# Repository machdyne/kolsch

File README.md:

# Kölsch Computer

Kölsch is an FPGA computer based on the GateMate A1.

This repo contains schematics, PCB layouts, pinouts, a 3D-printable case, example gateware and documentation.

Find more information on the [Kölsch product page](https://machdyne.com/product/kolsch-computer/).

## Programming Kölsch 

Kölsch can be programmed over USB-C or by copying gateware to a MicroSD card. The FPGA is configured by the onboard RP2040, which can load the configuration from onboard flash, a FAT-formatted MicroSD card or over the USB-JTAG bridge.

### JTAG

Program the FPGA configuration SRAM:

```
openFPGALoader -c dirtyJtag image.bit
```

## Examples

In order to build the examples, first edit rtl/config.mk and set the paths to the location of your toolchain. You can download the toolchain from [Cologne Chip](https://colognechip.com).

You can build each example with:

```
$ make && make impl
```

### 3.5mm TRRS Audio Jack

| Pin | Signal |
| --- | ------ |
| T | Left Audio |
| R1 | Right Audio |
| R2 | Composite Video |
| S | GND |

## Resources

 * [fpga-dac audio player](https://github.com/machdyne/fpga-dac)

## Board Revisions

| Revision | Notes |
| -------- | ----- |
| V2 | Initial production version |

## Funding

This project was partially funded through the NGI0 Entrust Fund, a fund established by NLnet with financial support from the European Commission's Next Generation Internet programme.

## License

This project is released under the [CERN-OHL-P](LICENSE.txt) license.

Note: You can use these designs for commercial purposes but we ask that instead of producing exact clones, that you either replace our trademarks and logos with your own or add your own next to ours.

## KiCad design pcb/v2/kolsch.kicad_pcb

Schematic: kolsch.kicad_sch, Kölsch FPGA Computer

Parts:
C1, C2, C3, C12, C16, C18, C19, C27, C28, C38, C39, C48, C49, C69, C70: 2.2uF; C_0603_1608Metric
C4, C5, C6, C21, C22, C29, C30, C41, C42, C50, C51, C75, C76: 470nF; C_0603_1608Metric
C7: 220nF; C_0402_1005Metric
C8, C9, C10, C11, C15, C17, C23, C24, C31, C32, C33, C34, C35, C43, C44, C45, C46, C47, C52, C53, C55, C56, C78, C79, C80, C81, C103, C104, C105, C106, C107: 100nF; C_0402_1005Metric
C13, C14, C25, C26: 10nF; C_0402_1005Metric
C20, C36, C37, C58, C59, C61, C62, C64, C65, C66, C67, C68, C71, C74, C77, C82, C84, C86, C87: 100nF; C_0603_1608Metric
C40, C72, C73, C97, C98, C101: 10uF; C_0603_1608Metric
C54, C57: 15pF; C_0603_1608Metric
C60, C63, C83, C85, C88: 1uF; C_0603_1608Metric
C89, C90, C91: 4.7uF; C_0603_1608Metric
C92: 10uF; R_0603_1608Metric
C93: 100nF; R_0603_1608Metric
C94, C95, C96: 10pF; C_0603_1608Metric
C99, C100, C102: 22uF; C_0603_1608Metric
C109, C110: 10uF; C_0402_1005Metric
D1: LED; LED_1206_3216Metric
FB3, FB4, FB5: Ferrite_Bead; R_0603_1608Metric
H1, H2, H3, H4: MountingHole_Pad; MountingHole_3.2mm_M3_Pad
J1: TYPE-C-31-M-12-FIXED; USB_C_Receptacle_HRO_TYPE-C-31-M-12-BIG-PADS-PASTE; PARTREV A
J2: USB_A_Stacked; USB_A_Wuerth_61400826021_Horizontal_Stacked
J3: AudioJack4; Jack_3.5mm_PJ320D_Horizontal
J4: MICROSD; SDCARD
L1, L2, L3: 2.2uH; L_Taiyo-Yuden_MD-4040
PMOD1: PMOD-Device-x2-Type-1A-GPIO; PMOD_2x06_HOST
R1, R3, R4, R5, R8: 4K7; R_0603_1608Metric
R2, R10: 5K1; R_0603_1608Metric
R6, R7: 27R; R_0603_1608Metric
R9, R17, R18, R26, R27, R28, R29, R40, R41: 0R; LD-NETTIE-0603
R11, R12, R20, R21: 15K; R_0402_1005Metric
R13, R14, R15, R16: 22R; R_0402_1005Metric
R19, R58, R65: 200K; R_0603_1608Metric
R30, R35, R38, R45, R49, R53: 1K; R_0603_1608Metric
R31, R32, R63, R64: 100R; R_0603_1608Metric
R33, R42, R43, R47, R51: 270R; R_0603_1608Metric
R34, R44, R48, R52: 536R; R_0603_1608Metric
R36: 2K; R_0603_1608Metric
R37: 10K; R_0603_1608Metric
R39: 33R; R_0603_1608Metric
R46, R50, R54: 2K2; R_0603_1608Metric
R55, R56, R57: 68R; R_0603_1608Metric
R59, R60, R61, R62: 20K; R_0603_1608Metric
R66: 44K2; R_0603_1608Metric
R67: 150K; R_0603_1608Metric
R68: 47K; R_0603_1608Metric
R69: 100K; R_0603_1608Metric
R70: 120K; R_0603_1608Metric
R73: 22R; R_0603_1608Metric
SW1: BOOT; Button_2P_3x4mm
TP1: TP_PWR1V8; TestPoint_THTPad_D1.0mm_Drill0.5mm
TP2: TP_PWR3V3; TestPoint_THTPad_D1.0mm_Drill0.5mm
TP3: TP_PWR2V5; TestPoint_THTPad_D1.0mm_Drill0.5mm
TP4: TP_PWR1V1; TestPoint_THTPad_D1.0mm_Drill0.5mm
U1: CCGM1A1; BGA-324_15.0x15.0mm_Layout18x18_P0.8mm_Ball0.5mm_Pad0.4mm_N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
U2: W989D6DBGX6; W989D6DB; PARTREV A05
U3, U8: LSF0108PWR; TSSOP-20_4.4x6.5mm_P0.65mm
U4: RP2040; RP2040-QFN-56-OFFICIAL; PARTREV 1.6.1
U5: AT25FF321A-SSHN-B; SOIC-8_3.9x4.9mm_P1.27mm
U6: 48MHz; OSC_KC2016Z13.5600C1KX00
U7: NCP164ASN180T1G; SOT-23-5
U9, U10, U11: TLV62569DDC; SOT-23-6
VGA1: DB15_Female_MountingHoles; DSUB-15-HD_Female_Horizontal_P2.29x1.98mm_EdgePinOffset3.03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
Y1: ECS-80-12-33-JGN-TR-12MHZ; XTAL_ECS-240-8-33-AGN-TR

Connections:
/AUDIO_L: R31.1, U1.A9 (IO_NB_B0)
/AUDIO_LC: C72.1, J3.T
/AUDIO_R: R32.1, U1.B9 (IO_NB_A0)
/AUDIO_RC: C73.1, J3.R1
/BOOT: R38.1, SW1.1
/CDONE: U1.V3 (IO_WA_B2/CFG_DONE), U4.27 (GPIO16)
/CFAILED: R1.2, U1.V2 (IO_WA_A2/~CFG_FAILED), U4.28 (GPIO17)
/CFG_MD2: U1.U4 (CFG_MD2/IO_WA_A1), U4.18 (GPIO15)
/CFG_MD3: U1.V4 (CFG_MD3/IO_WA_B1), U4.17 (GPIO14)
/CLK48: U1.N14 (CLK0/IO_SB_A8), U6.3 (CLK)
/CRESET: U1.T15 (~RESET), U4.11 (GPIO8)
/CSD_MISO: U1.E2 (IO_WC_B3), U3.6 (A4), U4.6 (GPIO4)
/CSD_MOSI: U1.E1 (IO_WC_A3), U3.5 (A3), U4.9 (GPIO7)
/CSD_SCK: U1.E3 (IO_WC_A4), U3.4 (A2), U4.8 (GPIO6)
/CSD_SS: U1.D2 (IO_WC_B5), U3.3 (A1), U4.7 (GPIO5)
/CUSB1_DN: U1.H2 (IO_WB_B7), U3.10 (A8), U4.13 (GPIO10)
/CUSB1_DP: U1.H1 (IO_WB_A7), U3.9 (A7), U4.14 (GPIO11)
/CUSB2_DN: U1.K2 (IO_WB_B5), U3.8 (A6), U4.15 (GPIO12)
/CUSB2_DP: U1.K1 (IO_WB_A5), U3.7 (A5), U4.16 (GPIO13)
/DRAM_A0: U1.K18 (IO_EA_A2), U2.H7 (A0)
/DRAM_A1: U1.P18 (IO_SB_B2), U2.H8 (A1)
/DRAM_A2: U1.N15 (IO_SB_B8), U2.J8 (A2)
/DRAM_A3: U1.K17 (IO_EA_B2), U2.J7 (A3)
/DRAM_A4: U1.M14 (IO_EA_B0), U2.J3 (A4)
/DRAM_A5: U1.M15 (IO_EA_A0), U2.J2 (A5)
/DRAM_A6: U1.P15 (IO_SB_B6), U2.H3 (A6)
/DRAM_A7: U1.M17 (IO_SB_A3), U2.H2 (A7)
/DRAM_A8: U1.L16 (IO_EA_A1), U2.H1 (A8)
/DRAM_A9: U1.U18 (IO_SB_B0), U2.G3 (A9)
/DRAM_A10: U1.P17 (IO_SB_A2), U2.H9 (A10)
/DRAM_A11: U1.U17 (IO_SB_A0), U2.G2 (A11)
/DRAM_A12: U1.L15 (IO_EA_B1), U2.G1 (A12)
/DRAM_BS0: U1.J17 (IO_EA_B4), U2.G7 (BA0)
/DRAM_BS1: U1.R18 (IO_SB_B1), U2.G8 (BA1)
/DRAM_CAS: U1.M18 (IO_SB_B3), U2.F7 (~CAS)
/DRAM_CKE: U1.R10 (IO_SA_A7), U2.F3 (CKE)
/DRAM_CLK: U1.R9 (IO_SA_A6), U2.F2 (CLK)
/DRAM_CS: U1.R17 (IO_SB_A1), U2.G9 (~CS)
/DRAM_DQ0: U1.V8 (IO_SA_B5), U2.A8 (DQ0)
/DRAM_DQ1: U1.T8 (IO_SA_B4), U2.B9 (DQ1)
/DRAM_DQ2: U1.U8 (IO_SA_A5), U2.B8 (DQ2)
/DRAM_DQ3: U1.P13 (IO_SB_B7), U2.C9 (DQ3)
/DRAM_DQ4: U1.T10 (IO_SA_B7), U2.C8 (DQ4)
/DRAM_DQ5: U1.P14 (CLK2/IO_SB_A6), U2.D9 (DQ5)
/DRAM_DQ6: U1.T9 (IO_SA_B6), U2.D8 (DQ6)
/DRAM_DQ7: U1.V10 (IO_SA_B8), U2.E9 (DQ7)
/DRAM_DQ8: U1.R7 (IO_SA_A2), U2.E1 (DQ8)
/DRAM_DQ9: U1.R8 (IO_SA_A4), U2.D2 (DQ9)
/DRAM_DQ10: U1.T7 (IO_SA_B2), U2.D1 (DQ10)
/DRAM_DQ11: U1.V5 (IO_SA_B0), U2.C2 (DQ11)
/DRAM_DQ12: U1.U5 (IO_SA_A0), U2.C1 (DQ12)
/DRAM_DQ13: U1.V7 (IO_SA_B3), U2.B2 (DQ13)
/DRAM_DQ14: U1.T6 (IO_SA_B1), U2.B1 (DQ14)
/DRAM_DQ15: U1.U7 (IO_SA_A3), U2.A2 (DQ15)
/DRAM_LDQM: U1.U10 (IO_SA_A8), U2.E8 (LDQM)
/DRAM_RAS: U1.R14 (IO_SB_B5), U2.F8 (~RAS)
/DRAM_UDQM: U1.R6 (IO_SA_A1), U2.F1 (UDQM)
/DRAM_WE: U1.R13 (CLK3/IO_SB_A5), U2.F9 (~WE)
/JTAG_TCK: R3.2, U1.R3 (JTAG_TCK/IO_WA_A5), U4.29 (GPIO18)
/JTAG_TDI: R5.2, U1.T2 (JTAG_TDI/IO_WA_A4), U4.31 (GPIO20)
/JTAG_TDO: R8.2, U1.U2 (JTAG_TDO/IO_WA_B3), U4.32 (GPIO21)
/JTAG_TMS: R4.2, U1.T3 (JTAG_TMS/IO_WA_B4), U4.30 (GPIO19)
/LED: R42.1, U1.A12 (IO_NB_B4)
/PMOD_A1: U1.D17 (IO_EB_B2), U8.3 (A1)
/PMOD_A1C: PMOD1.1 (IOA0), U8.18 (B1)
/PMOD_A2: U1.D18 (IO_EB_A2), U8.4 (A2)
/PMOD_A2C: PMOD1.2 (IOA1), U8.17 (B2)
/PMOD_A3: U1.E15 (IO_EB_B3), U8.5 (A3)
/PMOD_A3C: PMOD1.3 (IOA2), U8.16 (B3)
/PMOD_A4: U1.E16 (IO_EB_A3), U8.6 (A4)
/PMOD_A4C: PMOD1.4 (IOA3), U8.15 (B4)
/PMOD_A7: U1.F18 (IO_EB_A0), U8.7 (A5)
/PMOD_A7C: PMOD1.7 (IOB0), U8.14 (B5)
/PMOD_A8: U1.F17 (IO_EB_B0), U8.8 (A6)
/PMOD_A8C: PMOD1.8 (IOB1), U8.13 (B6)
/PMOD_A9: U1.F16 (IO_EB_A1), U8.9 (A7)
/PMOD_A9C: PMOD1.9 (IOB2), U8.12 (B7)
/PMOD_A10: U1.F15 (IO_EB_B1), U8.10 (A8)
/PMOD_A10C: PMOD1.10 (IOB3), U8.11 (B8)
/PWR1V0: C58.1, C61.1, C63.1, U4.23 (DVDD), U4.45 (VREG_VOUT), U4.50 (DVDD)
/PWR1V1: C1.2, C2.2, C4.2, C5.2, C9.2, C10.2, C13.2, C14.2, C18.2, C19.2, C20.2, C21.2, C22.2, C23.2, C24.2, C25.2, C26.2, C96.1, C99.1, C100.1, L3.2, R69.1, R73.2, TP4.1, U1.F9 (VDD), U1.G6 (VDD), U1.G8 (VDD), U1.G10 (VDD), U1.G12 (VDD), U1.H7 (VDD), U1.H9 (VDD), U1.H11 (VDD), U1.H13 (VDD), U1.J6 (VDD), U1.J8 (VDD), U1.J10 (VDD), U1.J12 (VDD), U1.K7 (VDD), U1.K9 (VDD), U1.K11 (VDD), U1.K13 (VDD), U1.L6 (VDD), U1.L8 (VDD), U1.L10 (VDD), U1.L12 (VDD), U1.M7 (VDD), U1.M9 (VDD), U1.M11 (VDD), U1.M13 (VDD), U1.N6 (VDD), U1.N8 (VDD), U1.N10 (VDD)
/PWR1V8: C84.1, C88.1, C103.2, C104.2, C105.2, C106.2, C107.2, C109.2, C110.2, R27.2, R28.2, R29.2, TP1.1, U2.A7 (VDDQ), U2.A9 (VDD), U2.B3 (VDDQ), U2.C7 (VDDQ), U2.D3 (VDDQ), U2.E7 (VDD), U2.J9 (VDD), U6.1 (INH), U6.4 (VCC), U7.5 (OUT)
/PWR2V5: C8.2, C16.2, C37.1, C60.1, C62.1, C64.1, C65.1, C68.1, C71.1, C74.1, C77.1, C82.1, C83.1, C87.1, C95.1, C98.1, L2.2, R1.1, R4.1, R5.1, R8.1, R9.2, R17.2, R18.2, R26.2, R40.2, R41.2, R67.1, TP3.1, U1.T14 (VDD_CLK), U3.2 (VREF_A), U4.1 (IOVDD), U4.10 (IOVDD), U4.22 (IOVDD), U4.26 (RUN), U4.33 (IOVDD), U4.42 (IOVDD), U4.43 (ADC_AVDD), U4.44 (VREG_VIN), U4.49 (IOVDD), U5.8 (VCC), U8.2 (VREF_A)
/PWR3V3: C59.1, C85.1, C92.1, C93.1, C94.1, C97.1, C101.1, J4.4 (VDD), L1.2, PMOD1.6 (VCC), PMOD1.12 (VCC), R19.1, R37.1, R58.1, R59.1, R60.1, R61.1, R62.1, R65.1, TP2.1, U4.48 (USB_VDD), U7.1 (IN), U7.3 (EN)
/PWR5V0: C89.1, C90.1, C91.1, FB3.1, FB4.1, FB5.1, U9.1 (EN), U9.4 (VIN), U10.1 (EN), U10.4 (VIN), U11.1 (EN), U11.4 (VIN)
/RP_QSPI_IO0: U4.53 (QSPI_SD0), U5.5 (DI(IO0))
/RP_QSPI_IO1: U4.55 (QSPI_SD1), U5.2 (DO(IO1))
/RP_QSPI_IO2: U4.54 (QSPI_SD2), U5.3 (IO2)
/RP_QSPI_IO3: U4.51 (QSPI_SD3), U5.7 (IO3)
/RP_QSPI_SCK: U4.52 (QSPI_SCLK), U5.6 (CLK)
/RP_QSPI_SS: R37.2, R38.2, U4.56 (QSPI_CSN), U5.1 (~CS)
/RSPI_MISO: U1.P1 (IO_WA_A7/SPI_D1), U4.40 (GPIO28/ADC2)
/RSPI_MOSI: U1.P2 (IO_WA_B7/SPI_D0), U4.39 (GPIO27/ADC1)
/RSPI_SCK: U1.N4 (IO_WA_B8/SPI_CLK), U4.38 (GPIO26/ADC0)
/RSPI_SS: U1.N3 (IO_WA_A8/~SPI_CS), U4.41 (GPIO29/ADC3)
/RUART_RX: U1.F3 (IO_WC_A2), U4.37 (GPIO25)
/RUART_TX: U1.G1 (IO_WC_A0), U4.36 (GPIO24)
/SD_MISO: J4.7 (DAT0), R62.2, U3.15 (B4)
/SD_MOSI: J4.3 (CMD), R60.2, U3.16 (B3)
/SD_SCK: J4.5 (CLK), R61.2, U3.17 (B2)
/SD_SS: J4.2 (DAT3/CD), R59.2, U3.18 (B1)
/SWCLK: U4.24 (SWCLK)
/SWD: U4.25 (SWD)
/USB1_CONN_DN: J2.2 (D1-), R14.1, R21.1
/USB1_CONN_DP: J2.3 (D1+), R13.1, R20.1
/USB1_DN: R14.2, U3.11 (B8)
/USB1_DP: R13.2, U3.12 (B7)
/USB2_CONN_DN: J2.6 (D2-), R12.1, R16.1
/USB2_CONN_DP: J2.7 (D2+), R11.1, R15.1
/USB2_DN: R16.2, U3.13 (B6)
/USB2_DP: R15.2, U3.14 (B5)
/USB_CONN_DN: J1.A7 (DN1), J1.B7 (DN2), R6.1
/USB_CONN_DP: J1.A6 (DP1), J1.B6 (DP2), R7.1
/USB_DN: R6.2, U4.46 (USB_DM)
/USB_DP: R7.2, U4.47 (USB_DP)
/VBUSC: FB3.2, FB4.2, J1.A4 (VBUS), J1.A9 (VBUS), J1.B4 (VBUS), J1.B9 (VBUS)
/VDD_EA: C39.2, C42.2, C44.2, C46.2, R27.1, U1.G14 (VDD_EA), U1.H17 (VDD_EA), U1.J14 (VDD_EA), U1.L14 (VDD_EA), U1.L17 (VDD_EA)
/VDD_EB: C38.2, C41.2, C43.2, C45.2, C47.2, R26.1, U1.A16 (VDD_EB), U1.B18 (VDD_EB), U1.E14 (VDD_EB), U1.E17 (VDD_EB), U1.F13 (VDD_EB)
/VDD_NA: C27.2, C29.2, C31.2, C33.2, C35.2, R17.1, U1.A5 (VDD_NA), U1.B7 (VDD_NA), U1.E6 (VDD_NA), U1.E8 (VDD_NA), U1.F7 (VDD_NA)
/VDD_NB: C28.2, C30.2, C32.2, C34.2, R18.1, U1.B10 (VDD_NB), U1.B13 (VDD_NB), U1.E10 (VDD_NB), U1.E12 (VDD_NB), U1.F11 (VDD_NB)
/VDD_PLL: C7.2, C12.2, C102.2, R73.1, U1.P16 (VDD_PLL)
/VDD_SA: C49.2, C51.2, C53.2, C56.2, R29.1, U1.P6 (VDD_SA), U1.P8 (VDD_SA), U1.P10 (VDD_SA), U1.U6 (VDD_SA), U1.U9 (VDD_SA)
/VDD_SB: C48.2, C50.2, C52.2, C55.2, R28.1, U1.N11 (VDD_SB), U1.N13 (VDD_SB), U1.N18 (VDD_SB), U1.R15 (VDD_SB), U1.T18 (VDD_SB)
/VDD_WA: C3.2, C6.2, C11.2, C15.2, C17.2, R9.1, U1.N5 (VDD_WA), U1.P3 (VDD_WA), U1.P5 (VDD_WA), U1.T1 (VDD_WA), U1.U3 (VDD_WA)
/VDD_WB: C70.2, C76.2, C79.2, C81.2, R41.1, U1.H5 (VDD_WB), U1.J2 (VDD_WB), U1.K5 (VDD_WB), U1.M2 (VDD_WB), U1.M5 (VDD_WB)
/VDD_WC: C69.2, C75.2, C78.2, C80.2, R40.1, U1.A2 (VDD_WC), U1.C2 (VDD_WC), U1.D5 (VDD_WC), U1.F2 (VDD_WC), U1.F5 (VDD_WC)
/VGA_B0: R51.2, U1.C9 (IO_NA_A8)
/VGA_B1: R52.2, U1.C8 (IO_NA_A6)
/VGA_B2: R53.2, U1.C7 (IO_NA_A5)
/VGA_B3: R54.2, U1.C6 (IO_NA_A3)
/VGA_BLUE: R51.1, R52.1, R53.1, R54.1, R57.2
/VGA_B_CONN: R57.1, VGA1.3
/VGA_G0: R47.2, U1.C5 (IO_NA_B2)
/VGA_G1: R48.2, U1.B8 (IO_NA_B7)
/VGA_G2: R49.2, U1.A8 (IO_NA_A7)
/VGA_G3: R50.2, U1.B6 (IO_NA_B4)
/VGA_GREEN: R47.1, R48.1, R49.1, R50.1, R56.2
/VGA_G_CONN: R56.1, VGA1.2
/VGA_HS: R63.2, U1.A3 (IO_NA_A0)
/VGA_HS_CONN: R63.1, VGA1.13
/VGA_R0: R43.2, U1.A6 (IO_NA_A4)
/VGA_R1: R44.2, U1.B5 (IO_NA_A2)
/VGA_R2: R45.2, U1.A4 (IO_NA_A1)
/VGA_R3: R46.2, U1.B4 (IO_NA_B1)
/VGA_RED: R43.1, R44.1, R45.1, R46.1, R55.2
/VGA_R_CONN: R55.1, VGA1.1
/VGA_VS: R64.2, U1.B3 (IO_NA_B0)
/VGA_VS_CONN: R64.1, VGA1.14
/VIDEO_C: J3.R2, R39.2
/VIDEO_D0: R33.1, U1.A17 (IO_EB_B5)
/VIDEO_D1: R34.1, U1.C18 (IO_EB_A4)
/VIDEO_D2: R35.1, U1.C17 (IO_EB_B4)
/VIDEO_D3: R36.1, U1.B15 (IO_EB_A8)
/XIN: C54.2, U4.20 (XIN), Y1.1 (IN/OUT)
/XOUT: R30.2, U4.21 (XOUT)
GND: C1.1, C2.1, C3.1, C4.1, C5.1, C6.1, C7.1, C8.1, C9.1, C10.1, C11.1, C12.1, C13.1, C14.1, C15.1, C16.1, C17.1, C18.1, C19.1, C20.1, C21.1, C22.1, C23.1, C24.1, C25.1, C26.1, C27.1, C28.1, C29.1, C30.1, C31.1, C32.1, C33.1, C34.1, C35.1, C36.2, C37.2, C38.1, C39.1, C40.2, C41.1, C42.1, C43.1, C44.1, C45.1, C46.1, C47.1, C48.1, C49.1, C50.1, C51.1, C52.1, C53.1, C54.1, C55.1, C56.1, C57.2, C58.2, C59.2, C60.2, C61.2, C62.2, C63.2, C64.2, C65.2, C66.2, C67.2, C68.2, C69.1, C70.1, C71.2, C74.2, C75.1, C76.1, C77.2, C78.1, C79.1, C80.1, C81.1, C82.2, C83.2, C84.2, C85.2, C86.2, C87.2, C88.2, C89.2, C90.2, C91.2, C92.2, C93.2, C97.2, C98.2, C99.2, C100.2, C101.2, C102.1, C103.1, C104.1, C105.1, C106.1, C107.1, C109.1, C110.1, D1.1 (K), H1.1, H2.1, H3.1, H4.1, J1.A1 (GND), J1.A12 (GND), J1.B1 (GND), J1.B12 (GND), J1.S1 (SHIELD), J1.S2 (SHIELD), J1.S3 (SHIELD), J1.S4 (SHIELD), J2.4 (GND1), J2.8 (GND2), J2.9 (Shield), J3.S, J4.6 (VSS), PMOD1.5 (GND), PMOD1.11 (GND), R2.2, R3.1, R10.2, R11.2, R12.2, R20.2, R21.2, R66.2, R68.2, R70.2, SW1.2, U1.A1 (GND), U1.A7 (GND), U1.A10 (GND), U1.A13 (GND), U1.A18 (GND), U1.B16 (GND), U1.C1 (GND), U1.E5 (GND), U1.E7 (GND), U1.E9 (GND), U1.E11 (GND), U1.E13 (GND), U1.E18 (GND), U1.F1 (GND), U1.F6 (GND), U1.F8 (GND), U1.F10 (GND), U1.F12 (GND), U1.F14 (GND), U1.G5 (GND), U1.G7 (GND), U1.G9 (GND), U1.G11 (GND), U1.G13 (GND), U1.H6 (GND), U1.H8 (GND), U1.H10 (GND), U1.H12 (GND), U1.H14 (GND), U1.H18 (GND), U1.J1 (GND), U1.J5 (GND), U1.J7 (GND), U1.J9 (GND), U1.J11 (GND), U1.J13 (GND), U1.K6 (GND), U1.K8 (GND), U1.K10 (GND), U1.K12 (GND), U1.K14 (GND), U1.L5 (GND), U1.L7 (GND), U1.L9 (GND), U1.L11 (GND), U1.L13 (GND), U1.L18 (GND), U1.M1 (GND), U1.M6 (GND), U1.M8 (GND), U1.M10 (GND), U1.M12 (GND), U1.M16 (GND), U1.N7 (GND), U1.N9 (GND), U1.N12 (GND), U1.N17 (GND), U1.P4 (GND), U1.P7 (GND), U1.P9 (GND), U1.R5 (CFG_MD0/IO_WA_A0), U1.R12 (GND), U1.R16 (GND), U1.T4 (GND), U1.T5 (CFG_MD1/IO_WA_B0), U1.T11 (GND), U1.T17 (GND), U1.U1 (POR_EN/IO_WA_A3), U1.U14 (GND), U1.U15 (GND), U1.U16 (GND), U1.V1 (GND), U1.V6 (GND), U1.V9 (GND), U1.V14 (GND), U1.V16 (GND), U1.V18 (GND), U2.A1 (VSS), U2.A3 (VSSQ), U2.B7 (VSSQ), U2.C3 (VSSQ), U2.D7 (VSSQ), U2.E3 (VSS), U2.J1 (VSS), U3.1 (GND), U4.19 (TESTEN), U4.57 (GND), U5.4 (GND), U6.2 (GND), U7.2 (GND), U8.1 (GND), U9.2 (GND), U10.2 (GND), U11.2 (GND), VGA1.0 (PAD), VGA1.5, VGA1.6, VGA1.7, VGA1.8, VGA1.10, Y1.2 (GND), Y1.4 (GND)
unnamed: C66.1, C72.2, R31.2
unnamed: C67.1, C73.2, R32.2
unnamed: D1.2 (A), R42.2
unnamed: J1.A5 (CC1), R2.1
unnamed: J1.B5 (CC2), R10.1
unnamed: C40.1, FB5.2, J2.1 (VBUS1), J2.5 (VBUS2)
unnamed: R33.2, R34.2, R35.2, R36.2, R39.1
unnamed: C36.1, R19.2, U3.19 (VREF_B), U3.20 (EN)
unnamed: C86.1, R58.2, U8.19 (VREF_B), U8.20 (EN)
unnamed: C94.2, R65.2, R66.1, U9.6 (FB)
unnamed: L1.1, U9.3 (SW)
unnamed: C95.2, R67.2, R68.1, U10.6 (FB)
unnamed: L2.1, U10.3 (SW)
unnamed: C96.2, R69.2, R70.1, U11.6 (FB)
unnamed: L3.1, U11.3 (SW)
unnamed: C57.1, R30.1, Y1.3 (OUT/IN)

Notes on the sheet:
MICROSD
EAST
WEST
LPSDR
AUDIO/VIDEO
UART1 TX
C1=15pF, C2=15pF, CL=12pF, Cstray=5, (C1*C2)/(C1+C2)+Cstray == CL
SPI0 CSn
FPGA
Kölsch
0.6 * (1 + (150/47)) = 2.514
SPI1 RX
SYSTEM CLOCK
PMOD
NORTH
SPI1 TX
UART1 RX
0.6 * (1 + (100/120)) = 1.0999 (SPEED mode)
SUPERVISOR
DUAL USB HOST PORTS
12-bit VGA DAC (RGB444)
SPI0 TX
SPI1 SCK
POWER
SPI0 RX
0.6 * (1 + (200/44.2)) = 3.314
SPI0 SCK
USB POWER / CONFIG
SOUTH

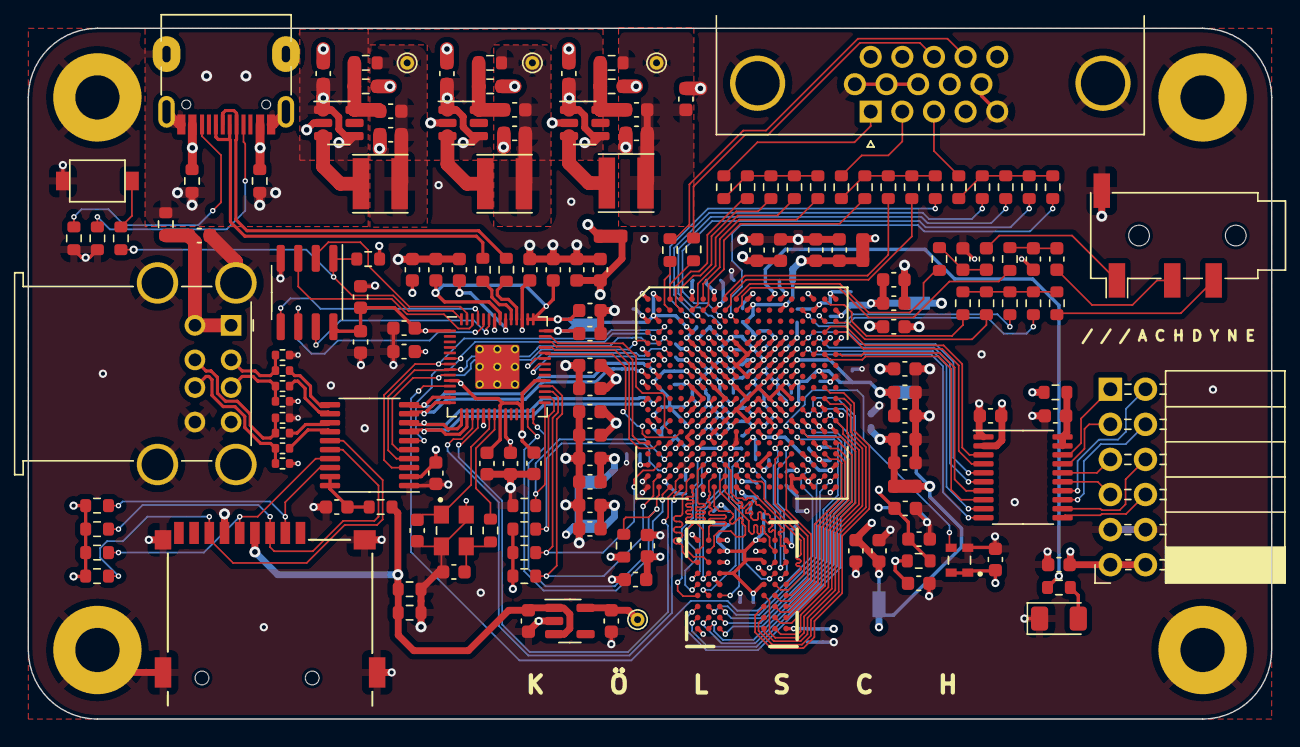
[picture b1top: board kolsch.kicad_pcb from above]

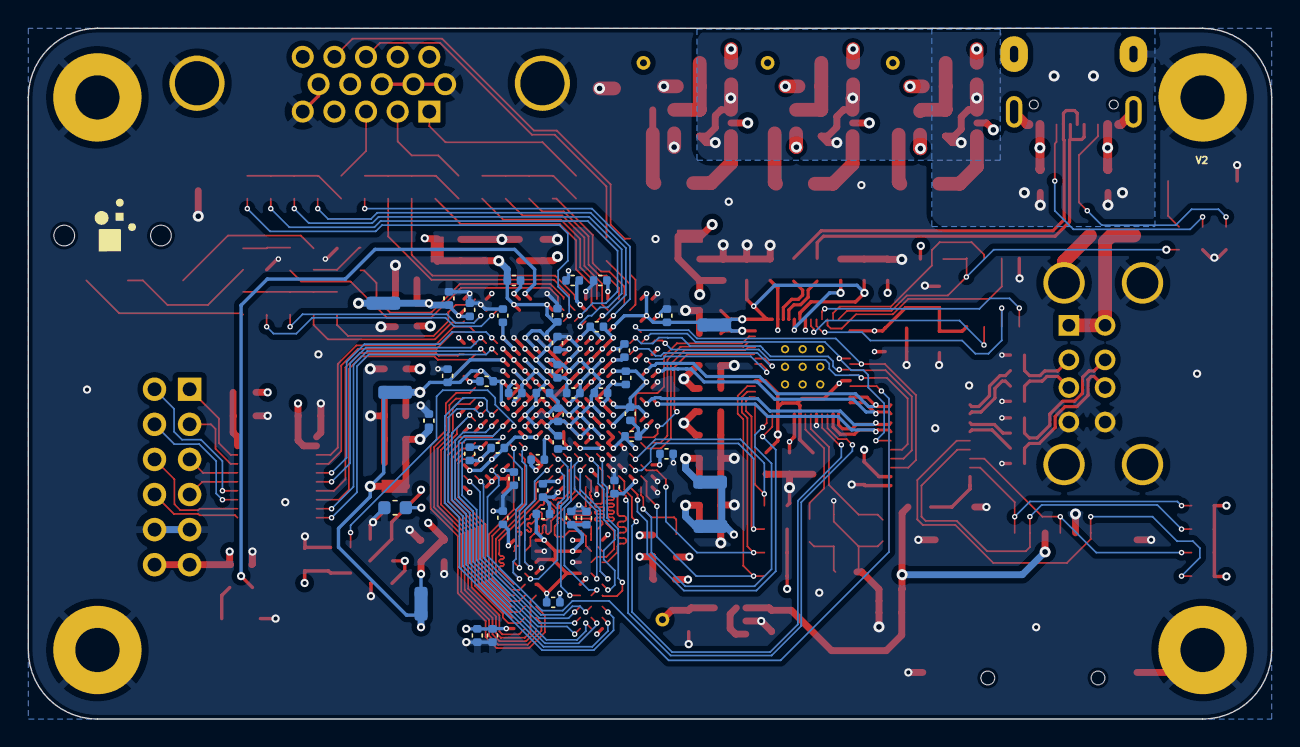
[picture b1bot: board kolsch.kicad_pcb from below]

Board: 4 copper layers, 90.0 x 50.0 mm, 210 parts (45 on the bottom side), 170 nets.

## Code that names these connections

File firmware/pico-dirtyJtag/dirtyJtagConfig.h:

#ifndef DirtyJtagConfig_h
#define DirtyJtagConfig_h

// Set to 0 to disable USB-CDC-UART bridge
#define USB_CDC_UART_BRIDGE  1


#define BOARD_PICO           0
#define BOARD_ADAFRUIT_ITSY  1
#define BOARD_SPOKE_RP2040   2
#define BOARD_QMTECH_RP2040_DAUGHTERBOARD 3
#define BOARD_WERKZEUG       4
#define BOARD_KOLSCH         100

// Select the board type from the above
#define BOARD_TYPE BOARD_KOLSCH
//#define BOARD_TYPE BOARD_ADAFRUIT_ITSY
//#define BOARD_TYPE BOARD_SPOKE_RP2040
//#define BOARD_TYPE BOARD_WERKZEUG
//#define BOARD_TYPE BOARD_QMTECH_RP2040_DAUGHTERBOARD

// General mapping
// TDI  SPIO RX
// TDO  SPIO TX
// TCK  SPIO SCK
// TMS  SPIO CS
// RST  GPIO
// TRST GPIO

#if ( BOARD_TYPE == BOARD_PICO )

#define PIN_TDI 16 
#define PIN_TDO 17
#define PIN_TCK 18
#define PIN_TMS 19
#define PIN_RST 20
#define PIN_TRST 21

#define LED_INVERTED   0
#define PIN_LED_TX     25
#define PIN_LED_ERROR  25
#define PIN_LED_RX     25

#if ( USB_CDC_UART_BRIDGE )
#define PIN_UART       uart0
#define PIN_UART_TX    12
#define PIN_UART_RX    13
#endif // USB_CDC_UART_BRIDGE

#elif ( BOARD_TYPE == BOARD_ADAFRUIT_ITSY )

#define PIN_TDI 28 
#define PIN_TDO 27
#define PIN_TCK 26
#define PIN_TMS 29
#define PIN_RST 24
#define PIN_TRST 25

// no regular LEDs on the Itsy - it's a neopixel
#define LED_INVERTED   0
#define PIN_LED_TX     -1
#define PIN_LED_ERROR  -1
#define PIN_LED_RX     -1

#if ( USB_CDC_UART_BRIDGE )
#define PIN_UART       uart0
#define PIN_UART_TX    0
#define PIN_UART_RX    1
#endif // USB_CDC_UART_BRIDGE

#elif ( BOARD_TYPE == BOARD_SPOKE_RP2040 )

#define PIN_TDI 23 
#define PIN_TDO 20
#define PIN_TCK 22
#define PIN_TMS 21
#define PIN_RST 26
#define PIN_TRST 27

#define LED_INVERTED   1
#define PIN_LED_TX     16
#define PIN_LED_ERROR  17
#define PIN_LED_RX     18

#if ( USB_CDC_UART_BRIDGE )
#define PIN_UART       uart0
#define PIN_UART_TX    28
#define PIN_UART_RX    29
#endif // USB_CDC_UART_BRIDGE


#elif ( BOARD_TYPE == BOARD_WERKZEUG )

#define PIN_TDI 1
#define PIN_TDO 2
#define PIN_TCK 0
#define PIN_TMS 3
#define PIN_RST 4
#define PIN_TRST 5

#define LED_INVERTED   1
#define PIN_LED_TX     20
#define PIN_LED_ERROR  21
#define PIN_LED_RX     20

#if ( USB_CDC_UART_BRIDGE )
#define PIN_UART       uart0
#define PIN_UART_TX    28
#define PIN_UART_RX    29
#endif // USB_CDC_UART_BRIDGE

#elif ( BOARD_TYPE == BOARD_KOLSCH )

#define PIN_TCK 18
#define PIN_TDI 20
#define PIN_TDO 21
#define PIN_TMS 19

#define PIN_RST 8
#define PIN_TRST 9

#define PIN_CDONE		16
#define PIN_CFAILED	17
#define PIN_CRESET	8
#define PIN_CFG_MD2	15
#define PIN_CFG_MD3	14

#define LED_INVERTED   1
#define PIN_LED_TX     1
#define PIN_LED_ERROR  2
#define PIN_LED_RX     3

#if ( USB_CDC_UART_BRIDGE )
#define PIN_UART       uart1
#define PIN_UART_TX    24
#define PIN_UART_RX    25
#endif // USB_CDC_UART_BRIDGE


#elif ( BOARD_TYPE == BOARD_QMTECH_RP2040_DAUGHTERBOARD )

// in rp2040 daughterboard UART pins are connected to FPGA pins
// depending on the FPGA pin configuration there is a possibility
// of damage so these pins are not going to be setup
#define USB_CDC_UART_BRIDGE  0

#define PIN_TDI  16 
#define PIN_TDO  17
#define PIN_TCK  18
#define PIN_TMS  19
// in rp2040 daughterboard these pins are connected to FPGA pins
// depending on the FPGA pin configuration there is a possibility
// of damage so these pins are not going to be setup
// #define PIN_RST  X
// #define PIN_TRST X

#define LED_INVERTED   0
#define PIN_LED_TX     25
#define PIN_LED_ERROR  25
#define PIN_LED_RX     25

#endif // BOARD_TYPE

#endif // DirtyJtagConfig_h

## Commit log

2024-03-19 rename kicad files
2024-03-19 add firmware
2025-06-05 update schematics
2025-06-24 latest kolsch firmware
2025-06-24 update makefile
2025-06-25 Toggle CRESET on jtag reset

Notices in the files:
pcb/v2/kolsch.kicad_sch:
Copyright © 2023 Lone Dynamics Corporation
